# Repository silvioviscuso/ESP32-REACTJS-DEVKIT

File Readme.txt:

files 

in folder files are managed like this
1) client requirement file
	
	this file contains files which you send me for project

2) Deliverables

	in this i generally add gerber and NC drill file but you will get these file in next 	folder

3) V*
	this file contains all project file, libraries, production data

	subfolders
	a) lib-  in this folder you will get components symbol and footprint library and also 		3D
	b) production data- 
		this folder contains these files
		BOM,DRC report, NCdrill , gerber, Pick&place,schematic,step, files

	c) apart from this you will get kicad project file in the folder just double click on 		file V1.kicad project file all files will automatically open in kicad

work which i made in PCB
1) Schematics
	some of the components are mapped wrongly
	pin map
	exact symbol matching

2) library
	created footprint and 3D library for components which are not previously included

3) PCB routing

	Changes in via size
	silkscreen text resize and alignment

..............................................

in this file deliverables-03-12-24
these are the changes

1)footprint pad size shorten
2) spi via correct
3) exit slope of esp
4) usb shield connnection

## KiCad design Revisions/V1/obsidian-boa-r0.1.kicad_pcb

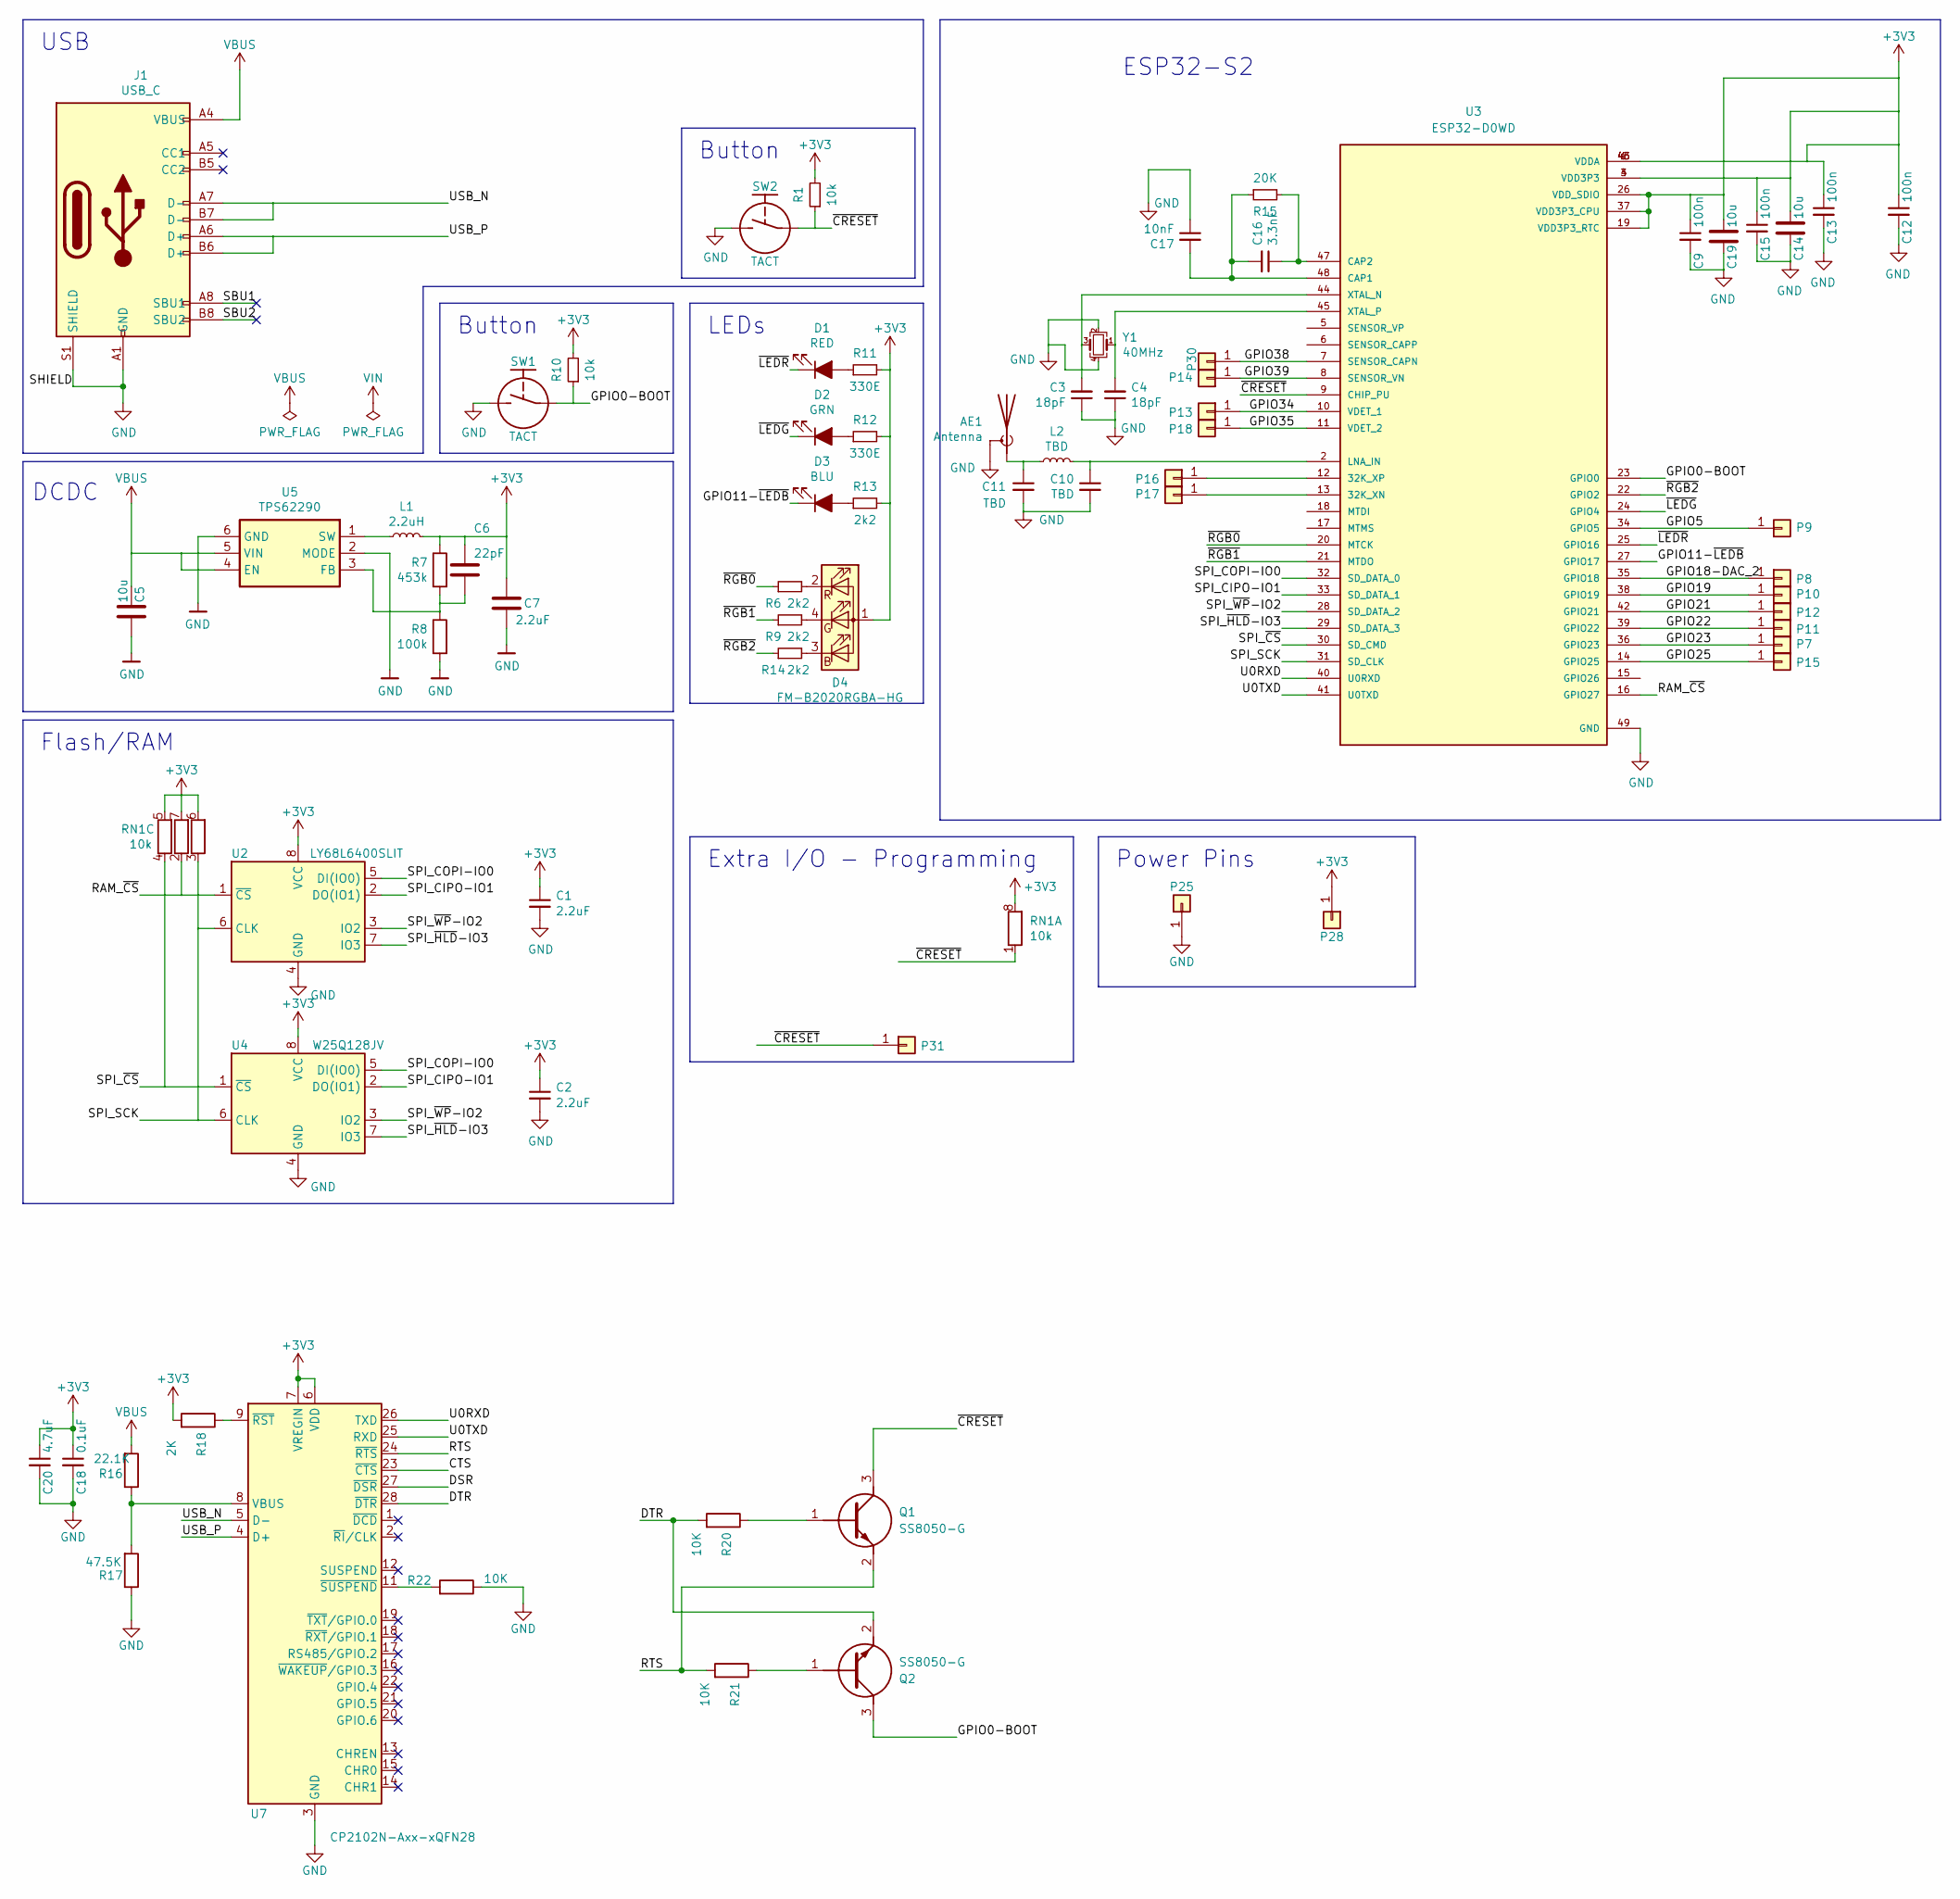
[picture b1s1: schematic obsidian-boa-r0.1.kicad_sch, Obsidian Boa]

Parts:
AE1: Antenna; 0479480001
C1, C2, C7: 2.2uF; C_0402_1005Metric
C3, C4: 18pF; C_0402_1005Metric
C5, C14, C19: 10u; C_0603_1608Metric
C6: 22pF; C_0402_1005Metric
C9, C12, C13, C15: 100n; C_0402_1005Metric
C10, C11: TBD; C_0402_1005Metric
C16: 3.3nF; C_0201_0603Metric
C17: 10nF; C_0402_1005Metric
C18: 0.1uF; C_0402_1005Metric
C20: 4.7uF; C_0402_1005Metric
D1: RED; LED_0603_1608Metric_Compact
D2: GRN; LED_0603_1608Metric_Compact
D3: BLU; LED_0603_1608Metric_Compact
D4: FM-B2020RGBA-HG; LED_Lumex_SML-LX0303SIUPGUSB
J1: USB_C; USB_C_Receptacle_HRO_TYPE-C-31-M-12
L1: 2.2uH; L_0805_2012Metric
L2: TBD; L_0402_1005Metric
P7: 7; Pin_Header_Straight_Round_1x01_Castellated
P8: 8; Pin_Header_Straight_Round_1x01_Castellated
P9: 9; Pin_Header_Straight_Round_1x01_Castellated
P10: 10; Pin_Header_Straight_Round_1x01_Castellated
P11: 11; Pin_Header_Straight_Round_1x01_Castellated
P12: 12; Pin_Header_Straight_Round_1x01_Castellated
P13: 13; Pin_Header_Straight_Round_1x01_Castellated
P14: 14; Pin_Header_Straight_Round_1x01_Castellated
P15: 15; Pin_Header_Straight_Round_1x01_Castellated
P16: 16; Pin_Header_Straight_Round_1x01_Castellated
P17: 17; Pin_Header_Straight_Round_1x01_Castellated
P18: 18; Pin_Header_Straight_Round_1x01_Castellated
P25: GND; Pin_Header_Straight_Round_1x01_Castellated
P28: 3V3; Pin_Header_Straight_Round_1x01_Castellated
P30: CDONE; Pin_Header_Straight_Round_1x01_Castellated
P31: CRESET; Pin_Header_Straight_Round_1x01_Castellated
Q1, Q2: SS8050-G; SOT95P240X115-3N; Mouser Part Number 750-SS8050-G
R1, R10: 10k; R_0402_1005Metric
R6, R9, R13, R14: 2k2; R_0402_1005Metric
R7: 453k; R_0402_1005Metric
R8: 100k; R_0402_1005Metric
R11, R12: 330E; R_0402_1005Metric
R15: 20K; R_0402_1005Metric
R16: 22.1K; R_0402_1005Metric
R17: 47.5K; R_0402_1005Metric
R18: 2K; R_0402_1005Metric
R20, R21, R22: 10K; R_0402_1005Metric
RN1: 10k; R_Array_Convex_4x0402
SW1, SW2: TACT; EVPBB2A9B000
U2: LY68L6400SLIT; SOIC-8_3.9x4.9mm_P1.27mm
U3: ESP32-D0WD; QFN48P700X700X90-49N; PARTREV 1.7
U4: W25Q128JV; SOIC-8_5.23x5.23mm_P1.27mm
U5: TPS62290; WSON-6-1EP_2x2mm_P0.65mm_EP1x1.6mm_ThermalVias
U7: CP2102N-Axx-xQFN28; QFN-28-1EP_5x5mm_P0.5mm_EP3.35x3.35mm
Y1: 40MHz; Crystal_SMD_Abracon_ABM10-4Pin_2.5x2.0mm

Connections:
+3V3: C1.1, C2.1, C6.1, C7.1, C9.1, C12.1, C13.1, C14.1, C15.1, C18.1, C19.1, C20.1, D4.1 (A), L1.2, P28.1, R1.2, R7.1, R10.2, R11.2, R12.2, R13.2, R18.2, RN1.5 (R4.2), RN1.6 (R3.2), RN1.7 (R2.2), RN1.8 (R1.2), U2.8 (VCC), U3.1 (VDDA), U3.3 (VDD3P3), U3.4 (VDD3P3), U3.19 (VDD3P3_RTC), U3.26 (VDD_SDIO), U3.37 (VDD3P3_CPU), U3.43 (VDDA), U3.46 (VDDA), U4.8 (VCC), U7.6 (VDD), U7.7 (VREGIN)
/CTS: U7.23 (~CTS)
/DSR: U7.27 (~DSR)
/DTR: Q2.2 (E), R20.2, U7.28 (~DTR)
/GPIO0-BOOT: Q2.3 (C), R10.1, SW1.1, SW1.2, U3.23 (GPIO0)
/GPIO5: P9.1, U3.34 (GPIO5)
/GPIO11-~LEDB: D3.1 (K), U3.27 (GPIO17)
/GPIO18-DAC_2: P8.1, U3.35 (GPIO18)
/GPIO19: P10.1, U3.38 (GPIO19)
/GPIO21: P12.1, U3.42 (GPIO21)
/GPIO22: P11.1, U3.39 (GPIO22)
/GPIO23: P7.1, U3.36 (GPIO23)
/GPIO25: P15.1, U3.14 (GPIO25)
/GPIO34: P13.1, U3.10 (VDET_1)
/GPIO35: P18.1, U3.11 (VDET_2)
/GPIO38: P30.1, U3.7 (SENSOR_CAPN)
/GPIO39: P14.1, U3.8 (SENSOR_VN)
/RAM_~CS: RN1.2 (R2.1), U2.1 (~CS), U3.16 (GPIO27)
/RTS: Q1.2 (E), R21.2, U7.24 (~RTS)
/SBU1: J1.A8 (SBU1)
/SBU2: J1.B8 (SBU2)
/SPI_CIPO-IO1: U2.2 (DO(IO1)), U3.33 (SD_DATA_1), U4.2 (DO(IO1))
/SPI_COPI-IO0: U2.5 (DI(IO0)), U3.32 (SD_DATA_0), U4.5 (DI(IO0))
/SPI_SCK: RN1.3 (R3.1), U2.6 (CLK), U3.31 (SD_CLK), U4.6 (CLK)
/SPI_~CS: RN1.4 (R4.1), U3.30 (SD_CMD), U4.1 (~CS)
/SPI_~HLD-IO3: U2.7 (IO3), U3.29 (SD_DATA_3), U4.7 (IO3)
/SPI_~WP-IO2: U2.3 (IO2), U3.28 (SD_DATA_2), U4.3 (IO2)
/U0RXD: U3.40 (U0RXD), U7.26 (TXD)
/U0TXD: U3.41 (U0TXD), U7.25 (RXD)
/USB_N: J1.A7 (D-), J1.B7 (D-), U7.5 (D-)
/USB_P: J1.A6 (D+), J1.B6 (D+), U7.4 (D+)
/~CRESET: P31.1, Q1.3 (C), R1.1, RN1.1 (R1.1), SW2.1, SW2.2, U3.9 (CHIP_PU)
/~LEDG: D2.1 (K), U3.24 (GPIO4)
/~LEDR: D1.1 (K), U3.25 (GPIO16)
/~RGB0: R6.1, U3.20 (MTCK)
/~RGB1: R9.1, U3.21 (MTDO)
/~RGB2: R14.1, U3.22 (GPIO2)
GND: AE1.2 (Shield), C1.2, C2.2, C3.1, C4.1, C5.2, C7.2, C9.2, C10.2, C11.2, C12.2, C13.2, C14.2, C15.2, C17.1, C18.2, C19.2, C20.2, J1.A1 (GND), J1.A12 (GND), J1.B1 (GND), J1.B12 (GND), J1.S1 (SHIELD), P25.1, R8.2, R17.1, R22.1, SW1.3, SW1.4, SW2.3, SW2.4, U2.4 (GND), U3.49 (GND), U4.4 (GND), U5.2 (MODE), U5.6 (GND), U5.7 (GND), U7.3 (GND), U7.29 (GND), Y1.2, Y1.4
unnamed: AE1.1 (A), C11.1, L2.2
unnamed: D1.2 (A), R11.1
unnamed: D2.2 (A), R12.1
unnamed: D3.2 (A), R13.1
unnamed: D4.3 (BK), R14.2
unnamed: D4.4 (GK), R9.2
unnamed: D4.2 (RK), R6.2
unnamed: P16.1, U3.12 (32K_XP)
unnamed: P17.1, U3.13 (32K_XN)
unnamed: Q1.1 (B), R20.1
unnamed: Q2.1 (B), R21.1
unnamed: C16.2, C17.2, R15.1, U3.48 (CAP1)
unnamed: C16.1, R15.2, U3.47 (CAP2)
unnamed: C10.1, L2.1, U3.2 (LNA_IN)
unnamed: C3.2, U3.44 (XTAL_N), Y1.3
unnamed: C4.2, U3.45 (XTAL_P), Y1.1
unnamed: C6.2, R7.2, R8.1, U5.3 (FB)
unnamed: L1.1, U5.1 (SW)
unnamed: R16.1, R17.2, U7.8 (VBUS)
unnamed: R18.1, U7.9 (~RST)
unnamed: R22.2, U7.11 (~SUSPEND)
VBUS: C5.1, J1.A4 (VBUS), J1.A9 (VBUS), J1.B4 (VBUS), J1.B9 (VBUS), R16.2, U5.4 (EN), U5.5 (VIN)

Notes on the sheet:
Power Pins
Button
LEDs
ESP32-S2
DCDC
Flash/RAM
Extra I/O - Programming
USB

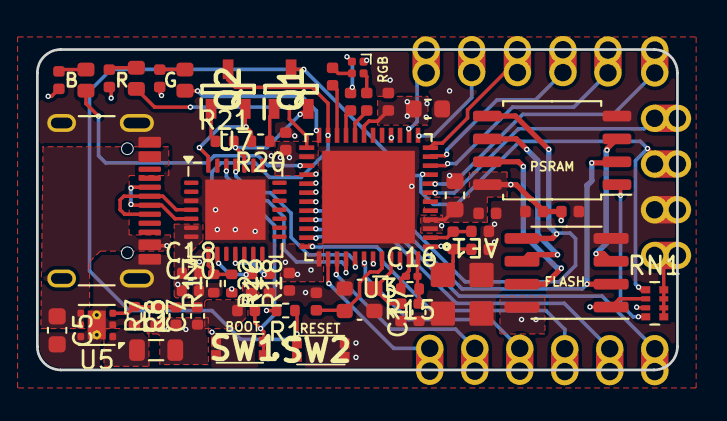
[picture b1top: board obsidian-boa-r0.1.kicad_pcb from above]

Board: 4 copper layers, 35.6 x 17.8 mm, 71 parts (0 on the bottom side), 56 nets.

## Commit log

2024-11-02 *STABLE V.0.1*
2024-11-06 *V4 STABLE*
2024-11-14 Versione 6
2024-12-04 *STABLE*
2024-12-05 *V9 - STABLE*
2024-12-06 Updated BOM file
2024-12-06 updated PICK & PLACE file

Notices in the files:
Revisions/V1/obsidian-boa-r0.1.kicad_pcb:
© 2020 Greg Davill
License: CC BY-SA 4.0
